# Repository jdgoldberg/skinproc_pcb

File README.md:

# skinproc_pcb
Eagle PCB for SkinProc project

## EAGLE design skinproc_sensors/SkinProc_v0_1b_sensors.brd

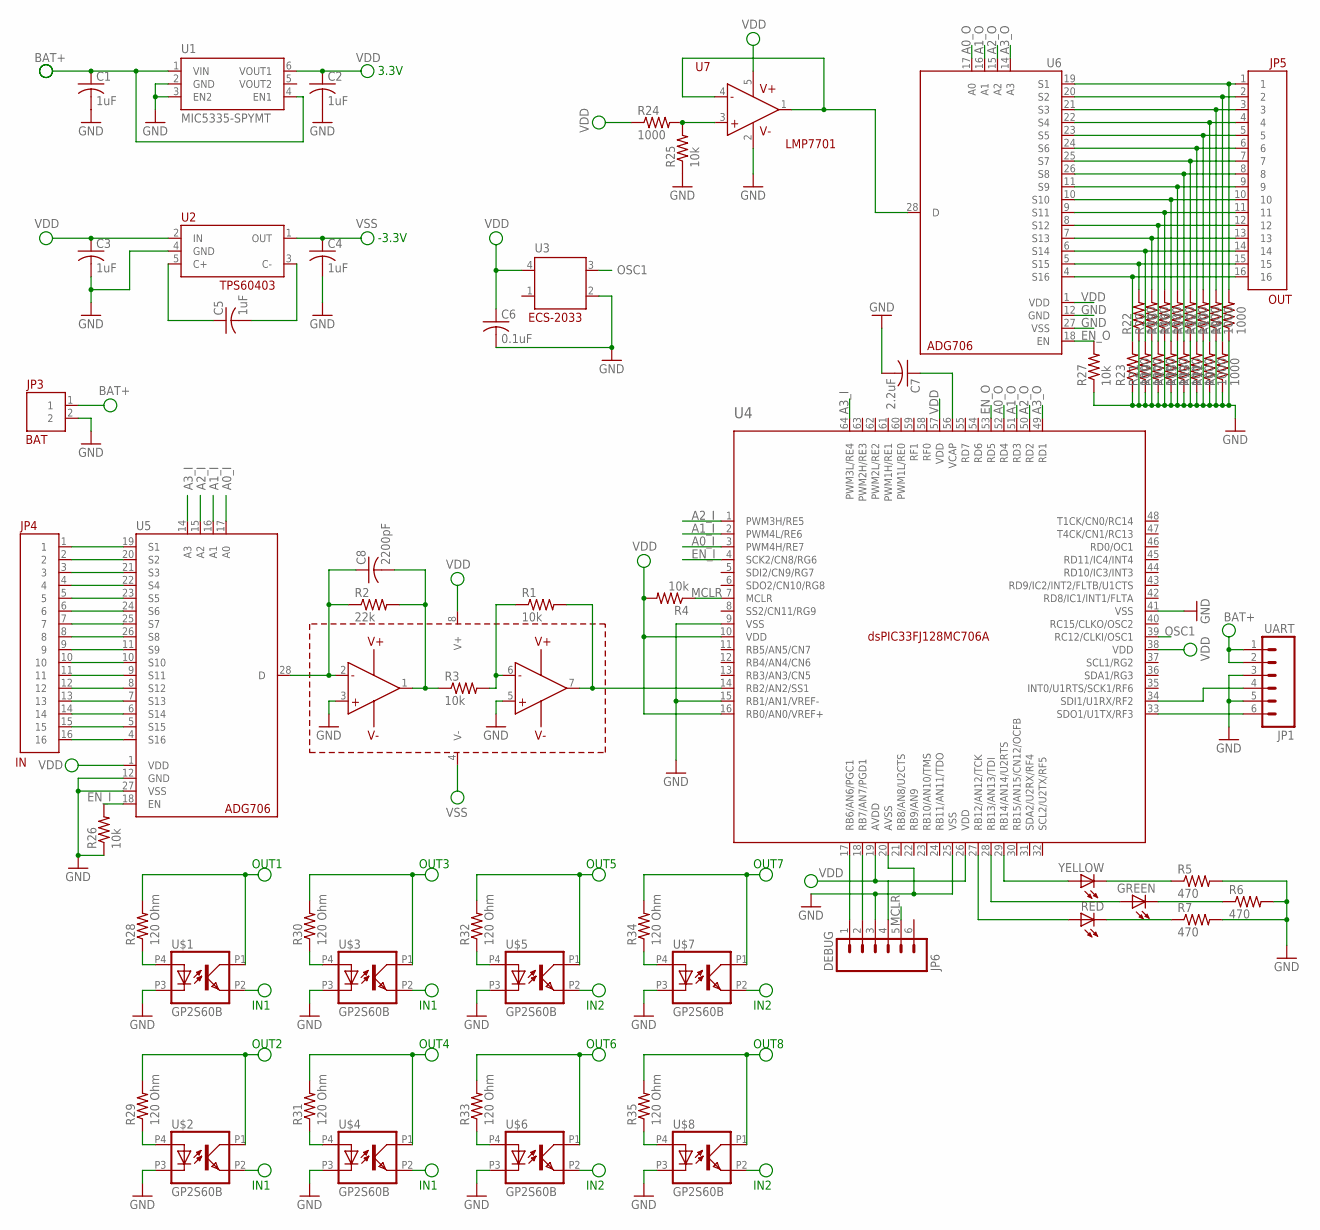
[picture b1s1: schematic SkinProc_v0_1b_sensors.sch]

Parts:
C1, C2, C3, C4, C5: 1uF; C0402
C6: 0.1uF; C0402
C7: 2.2uF; C0402
C8: 2200pF; C0402
GREEN: LEDCHIP-LED0603; CHIP-LED0603
JP1: UART; MOLEX_503480-0600
JP3: BAT; 2_PAD
JP4: IN; 16_PAD
JP5: OUT; 16_PAD
JP6: DEBUG; MOLEX_503480-0600
R1, R3, R4, R25, R26, R27: 10k; R0402
R2: 22k; R0402
R5, R6, R7: 470; R0402
R8, R9, R10, R11, R12, R13, R14, R15, R16, R17, R18, R19, R20, R21, R22, R23, R24: 1000; R0402
R28, R29, R30, R31, R32, R33, R34, R35: 120 Ohm; 0402-RES
RED: LEDCHIP-LED0603; CHIP-LED0603
U1: MIC5335-SPYMT; MLF-6
U2: TPS60403; SOT23-DBV
U3: OSCILLATORS; OSCILLATOR-SMD
U4: DSPIC33FJ128MC706-I/PT; TQFP64
U5, U6: ADG706; TSSOP28
U7: LMP7701; SOT23-DBV
U8: NATIONAL_OP_AMP; SO08
U$1, U$2, U$3, U$4, U$5, U$6, U$7, U$8: GP2S60B; 4-SMD
YELLOW: LEDCHIP-LED0603; CHIP-LED0603

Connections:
A0_I: U4.3 (PWM4H/RE7), U5.17 (A0)
A0_O: U4.52 (RD4), U6.17 (A0)
A1_I: U4.2 (PWM4L/RE6), U5.16 (A1)
A1_O: U4.51 (RD3), U6.16 (A1)
A2_I: U4.1 (PWM3H/RE5), U5.15 (A2)
A2_O: U4.50 (RD2), U6.15 (A2)
A3_I: U4.64 (PWM3L/RE4), U5.14 (A3)
A3_O: U4.49 (RD1), U6.14 (A3)
BAT+: C1.1, JP1.1, JP1.2, JP3.1, U1.1 (VIN), U1.4 (EN1)
EN_I: R26.2, U4.4 (SCK2/CN8/RG6), U5.18 (EN)
EN_O: R27.2, U4.53 (RD5), U6.18 (EN)
GND: C1.2, C2.2, C3.2, C4.2, C6.2, C7.2, JP1.3, JP1.5, JP3.2, JP6.3, R5.2, R6.2, R7.2, R8.1, R9.1, R10.1, R11.1, R12.1, R13.1, R14.1, R15.1, R16.1, R17.1, R18.1, R19.1, R20.1, R21.1, R22.1, R23.1, R25.1, R26.1, R27.1, U1.2 (GND), U1.3 (EN2), U2.4 (GND), U3.2 (GND), U4.9 (VSS), U4.15 (RB1/AN1/VREF-), U4.20 (AVSS), U4.25 (VSS), U4.41 (VSS), U5.12 (GND), U5.27 (VSS), U6.12 (GND), U6.27 (VSS), U7.2 (V-), U8.3 (+A), U8.5 (+B), U$1.P3 (3), U$2.P3 (3), U$3.P3 (3), U$4.P3 (3), U$5.P3 (3), U$6.P3 (3), U$7.P3 (3), U$8.P3 (3)
IN1: JP4.1, U5.19 (S1), U$1.P2 (2), U$2.P2 (2), U$3.P2 (2), U$4.P2 (2)
IN2: JP4.2, U5.20 (S2), U$5.P2 (2), U$6.P2 (2), U$7.P2 (2), U$8.P2 (2)
IN3: JP4.3, U5.21 (S3)
IN4: JP4.4, U5.22 (S4)
IN5: JP4.5, U5.23 (S5)
IN6: JP4.6, U5.24 (S6)
IN7: JP4.7, U5.25 (S7)
IN8: JP4.8, U5.26 (S8)
IN9: JP4.9, U5.11 (S9)
IN10: JP4.10, U5.10 (S10)
IN11: JP4.11, U5.9 (S11)
IN12: JP4.12, U5.8 (S12)
IN13: JP4.13, U5.7 (S13)
IN14: JP4.14, U5.6 (S14)
IN15: JP4.15, U5.5 (S15)
IN16: JP4.16, U5.4 (S16)
MCLR: JP6.5, R4.1, U4.7 (MCLR)
unnamed: R1.2, U4.14 (RB2/AN2/SS1), U8.7 (VOUTB)
unnamed: C5.1, U2.5 (C+)
unnamed: C7.1, U4.56 (VCAP)
unnamed: C5.2, U2.3 (C-)
unnamed: R5.1, YELLOW.C
unnamed: R28.1, U$1.P4 (4)
unnamed: JP6.1, U4.17 (RB6/AN6/PGC1)
unnamed: R1.1, R3.2, U8.6 (-B)
unnamed: C8.2, R2.2, R3.1, U8.1 (VOUTA)
unnamed: JP6.2, U4.18 (RB7/AN7/PGD1)
unnamed: C8.1, R2.1, U5.28 (D), U8.2 (-A)
unnamed: JP1.4, U4.34 (SDI1/U1RX/RF2)
unnamed: JP1.6, U4.33 (SDO1/U1TX/RF3)
unnamed: R7.1, RED.C
unnamed: GREEN.C, R6.1
unnamed: U4.29 (RB14/AN14/U2RTS), YELLOW.A
unnamed: GREEN.A, U4.28 (RB13/AN13/TDI)
unnamed: RED.A, U4.27 (RB12/AN12/TCK)
unnamed: R29.1, U$2.P4 (4)
unnamed: R30.1, U$3.P4 (4)
unnamed: R31.1, U$4.P4 (4)
unnamed: U6.28 (D), U7.1 (VOUT), U7.4 (-)
unnamed: R32.1, U$5.P4 (4)
unnamed: R33.1, U$6.P4 (4)
unnamed: R34.1, U$7.P4 (4)
unnamed: R35.1, U$8.P4 (4)
unnamed: R24.2, R25.2, U7.3 (+)
OSC1: U3.3 (OUT), U4.39 (RC12/CLKI/OSC1)
OUT1: JP5.1, R8.2, R28.2, U6.19 (S1), U$1.P1 (1)
OUT2: JP5.2, R9.2, R29.2, U6.20 (S2), U$2.P1 (1)
OUT3: JP5.3, R10.2, R30.2, U6.21 (S3), U$3.P1 (1)
OUT4: JP5.4, R11.2, R31.2, U6.22 (S4), U$4.P1 (1)
OUT5: JP5.5, R12.2, R32.2, U6.23 (S5), U$5.P1 (1)
OUT6: JP5.6, R13.2, R33.2, U6.24 (S6), U$6.P1 (1)
OUT7: JP5.7, R14.2, R34.2, U6.25 (S7), U$7.P1 (1)
OUT8: JP5.8, R15.2, R35.2, U6.26 (S8), U$8.P1 (1)
OUT9: JP5.9, R16.2, U6.11 (S9)
OUT10: JP5.10, R17.2, U6.10 (S10)
OUT11: JP5.11, R18.2, U6.9 (S11)
OUT12: JP5.12, R19.2, U6.8 (S12)
OUT13: JP5.13, R20.2, U6.7 (S13)
OUT14: JP5.14, R21.2, U6.6 (S14)
OUT15: JP5.15, R22.2, U6.5 (S15)
OUT16: JP5.16, R23.2, U6.4 (S16)
VDD: C2.1, C3.1, C6.1, JP6.4, R4.2, R24.1, U1.6 (VOUT1), U2.2 (IN), U3.4 (VDD), U4.10 (VDD), U4.16 (RB0/AN0/VREF+), U4.19 (AVDD), U4.26 (VDD), U4.38 (VDD), U4.57 (VDD), U5.1 (VDD), U6.1 (VDD), U7.5 (V+), U8.8 (V+)
VSS: C4.1, U2.1 (OUT), U8.4 (V-)

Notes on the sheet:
3.3V
-3.3V
IN1
OUT1
OUT2
OUT3
OUT4
IN2
OUT5
OUT6
OUT8
OUT7

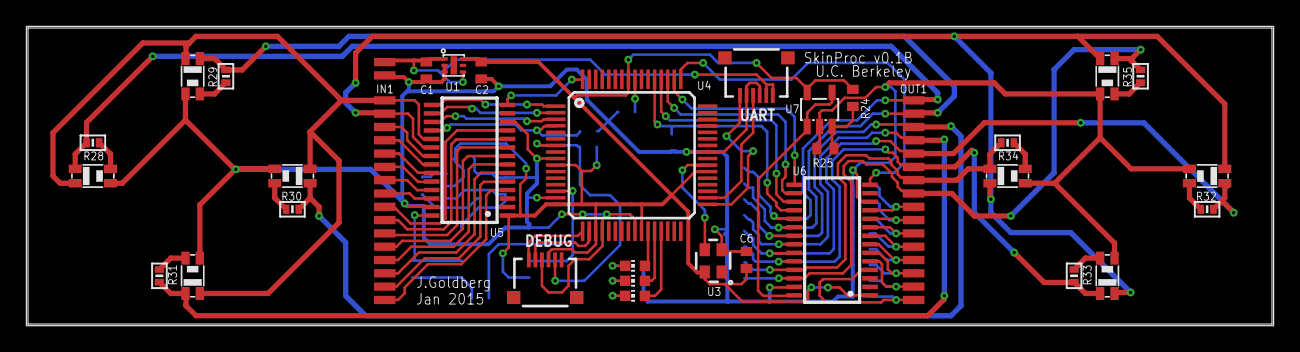
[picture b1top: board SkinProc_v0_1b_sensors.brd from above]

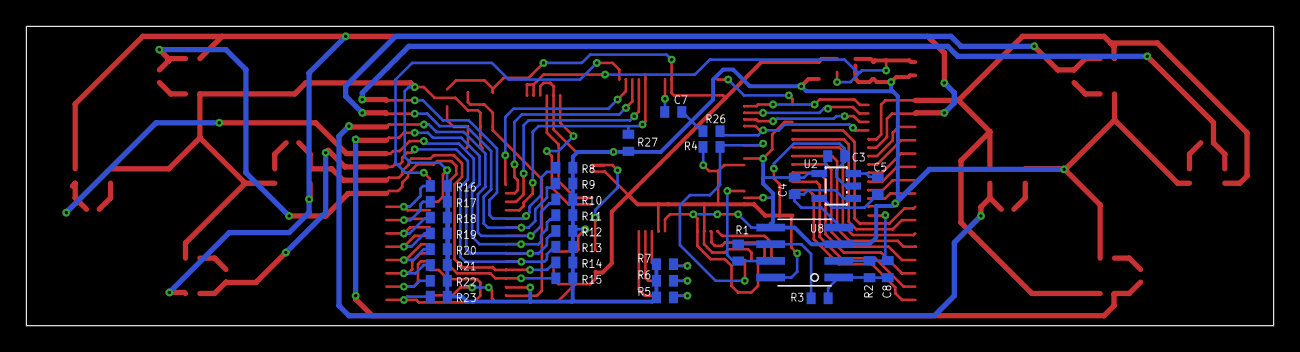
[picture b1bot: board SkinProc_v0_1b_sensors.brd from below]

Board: 2 copper layers, 95.2 x 22.9 mm, 67 parts (32 on the bottom side), 75 nets.

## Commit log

2015-05-15 First commit. Uploading schematics and boards.
